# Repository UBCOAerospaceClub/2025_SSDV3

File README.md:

# The Super Step Down V3

The SSDV3 is an independently-made, non-isolated DC/DC converter designed for unmanned aerial systems (UAS). The module is intended for converting 50V battery input down to 5-12V output at a maximum load of 8A. It acts as a reliable battery-eliminator circuit (BEC) through effective regulation in the presence of large line voltage and load current transients.

## Comparison with Last Super Step Down

This design is motivated by the challenges encountered by the [UBCO Aerospace Club](https://github.com/UBCOAerospaceClub) with their Jellyfish quadcopter when powering auxiliary electronics off the drone's main battery. Lessons were learned through a variety of integration failures, investigations, and verification, and these experiences informed the development of version 3 of the Super Step Down series.

**Improvements from the previous version:**

- Dramatically improved regulation during line and load transients
- Considerable footprint area reduction by 16.5%
- Configurable output voltages instead of a fixed 5V output
- Added ESD protection on inputs
- Features reverse polarity protection
- Uses direct solder pads instead of terminal block for output connection

## Documentation

[Super Step Down V3 Documentation](https://docs.google.com/document/d/1HDTwUbcQu91JqGZ-epUO-CT9nVxvoZJ6mtjSmItczHE/edit?usp=sharing)

## Specifications

<table><tbody>
  <tr>
    <td>Input Voltage</td>
    <td>20-60V</td>
  </tr>
  <tr>
    <td>Max Transient Voltage</td>
    <td>100V (clamping starts at 70V)</td>
  </tr>
  <tr>
    <td>Output Voltage(s)</td>
    <td>5.1V, 7.4V, 12V</td>
  </tr>
  <tr>
    <td>Max Output Current*</td>
    <td>8A</td>
  </tr>
  <tr>
    <td>Typical Efficiency</td>
    <td>88%</td>
  </tr>
  <tr>
    <td>Voltage Transient Deviation</td>
    <td>±2.5%</td>
  </tr>
</tbody>
</table>

### Performance Curves

**Voltage ripple at 5.1V Output**

**Transient response of 5.1V 5-0A Output**

**Efficiency Measurements, 50-V Input**

## Copyright Notice

Copyright &#169; Julian Joaquin 2026

Documentation and media are licensed under CC BY-SA 4.0

Hardware Source Licensed under CERN-OHL-W version 2

UBCO is registered trademark of the University of British Columbia. The use of UBC trademarks in this project are only for identification, and do not indicate association or endorsement. For guidelines on the permitted uses of UBC trademarks, please see http://universitycounsel.ubc.ca/university-trade-marks/.

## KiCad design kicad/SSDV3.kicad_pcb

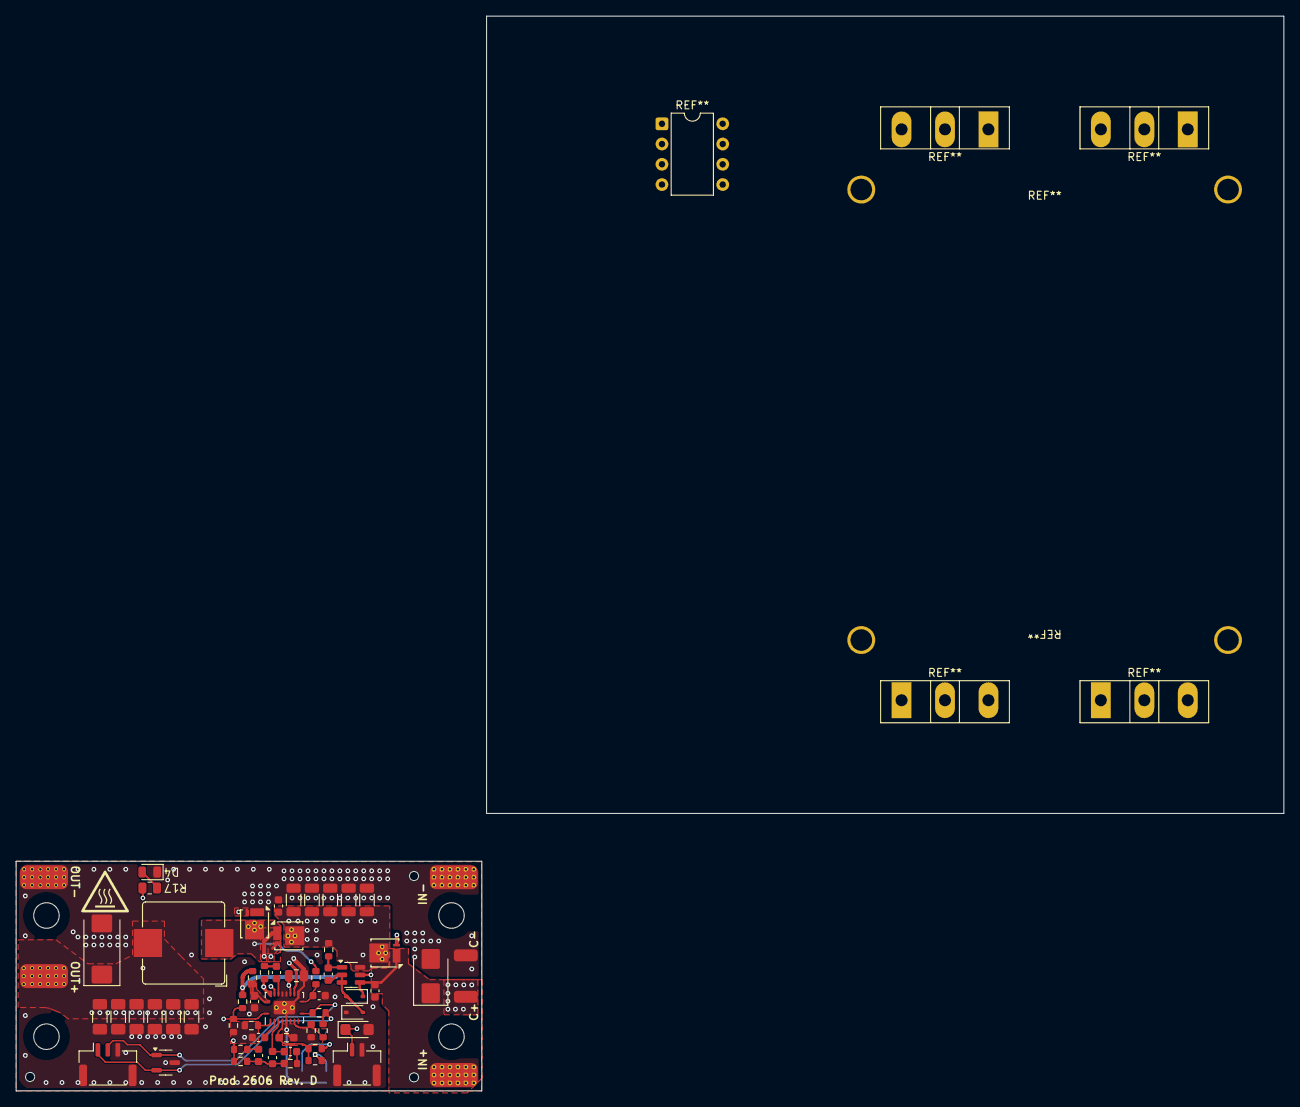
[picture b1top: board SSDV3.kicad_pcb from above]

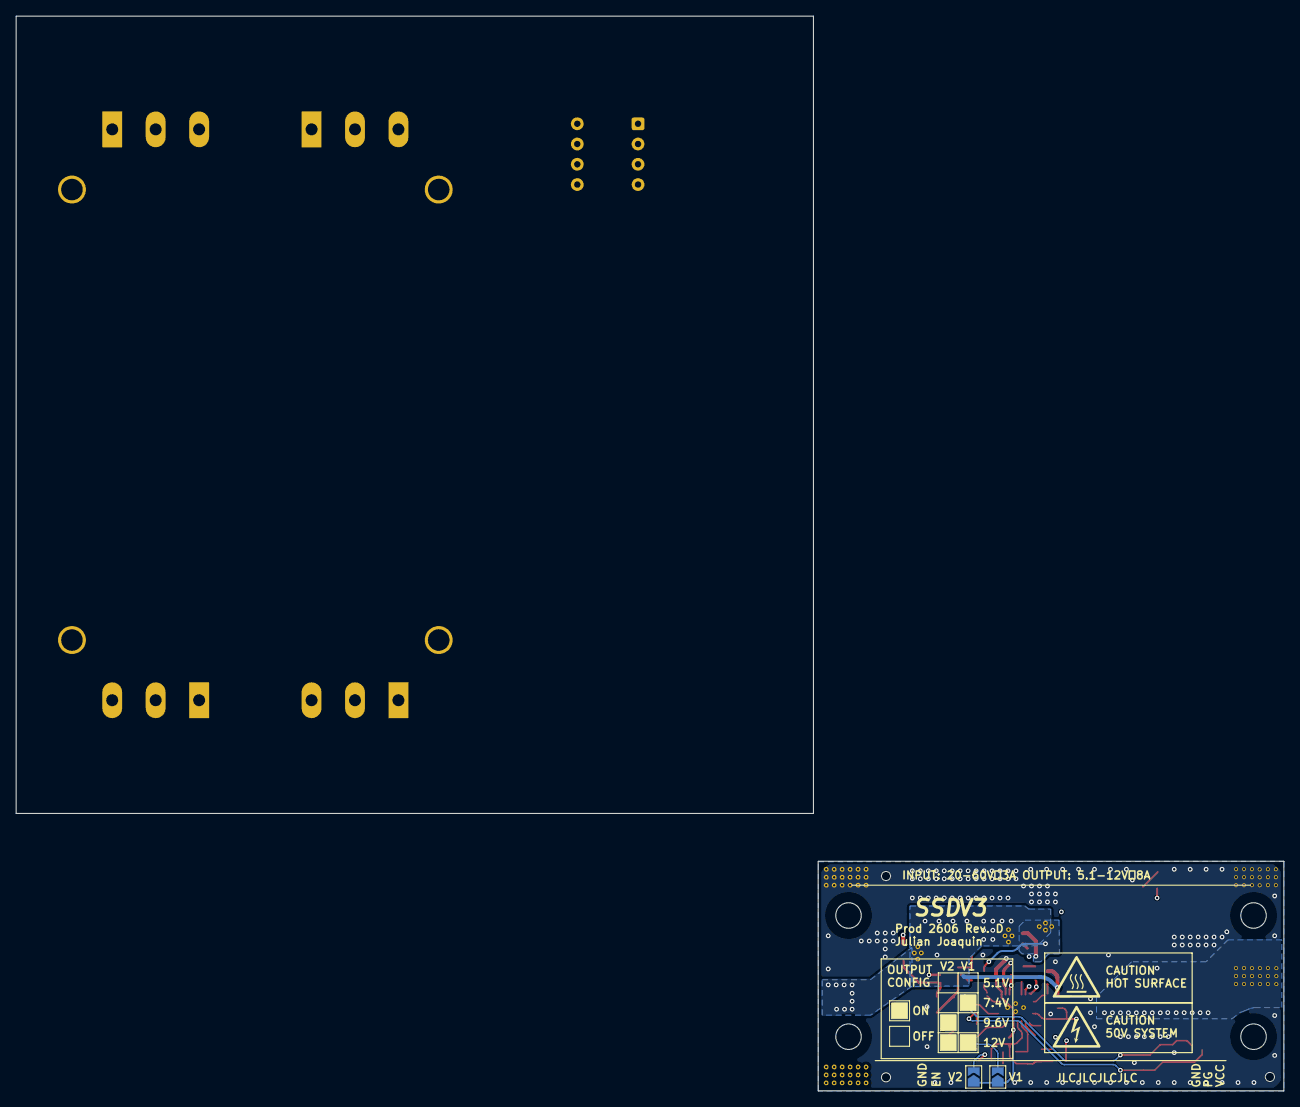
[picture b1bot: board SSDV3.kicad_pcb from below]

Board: 4 copper layers, 58.4 x 28.8 mm, 67 parts (3 on the bottom side), 28 nets.

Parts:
C2, C3, C4, C10, C13: 100nF; C_0603_1608Metric
C5, C6, C7, C8, C9: 4.7uF; C_1206_3216Metric
C11: 2.2uF; C_0805_2012Metric
C12: 47nF; C_0603_1608Metric
C14: 8.2pF; C_0603_1608Metric
C15: 1.5nF; C_0603_1608Metric
C16: 4.7nF; C_0603_1608Metric
C17: 68pF; C_0603_1608Metric
C18, C19, C20, C21, C22, C23: 22uF; C_1206_3216Metric_Pad1.33x1.80mm_HandSolder
C24: 100uF; CP_EIA-7343-20_Kemet-V_HandSolder
D1: 64V; D_SMB
D2, D3: BAT46WS; D_SOD-323
D4: GREEN; LED_0805_2012Metric
D5: 60V; D_SMF
D6: 8V; SOT-23-3
H1, H2, H3: MountingHole; ToolingHole_1.152mm
HS1: 241802B92200G; 24180xB9x200G
J1, J4, J5, J6: SolderPad; SolderWirePad_1x01_SMD_3x6mm
J2, J3: SolderPad; SolderWirePad_1x01_SMD_1.5x3mm
J7: SM02B-GHS-TB(LF)(SN); JST_GH_SM02B-GHS-TB_1x02-1MP_P1.25mm_Horizontal
J8: SM03B-GHS-TB(LF)(SN); JST_GH_SM03B-GHS-TB_1x03-1MP_P1.25mm_Horizontal
JP1: 7.4V; SolderJumper-2_P1.3mm_Open_TrianglePad1.0x1.5mm
JP2: 9.6V; SolderJumper-2_P1.3mm_Open_TrianglePad1.0x1.5mm
L1: 4.7uH; L_Bourns_SRP1038C_10.0x10.0mm
NT1: NetTie_2; NetTie-2_SMD_Pad0.5mm
Q1, Q2, Q3: BSZ146N10LS5; Infineon_PG-TSDSON-8-26_3.3x3.3mm_P0.65mm_ThermalVias-D0.3mm
R1, R11: 1.5k; R_0603_1608Metric
R2: 150k; R_0603_1608Metric
R3: 12k; R_0603_1608Metric
R4, R9: 2.2; R_0603_1608Metric
R5: 24k; R_0603_1608Metric
R6, R8, R12: 20k; R_0603_1608Metric
R7: 0; R_0603_1608Metric
R10: 560; R_0603_1608Metric
R13: 10k; R_0603_1608Metric
R14: 6.81k; R_0603_1608Metric
R15: 3.48k; R_0603_1608Metric
R16: 3.74k; R_0603_1608Metric_Pad0.98x0.95mm_HandSolder
R17: 1k; R_0805_2012Metric
U1: LM5050-1; TSOT-23-6
U2: LM5146; Texas_RGY0020B_EP_3.5x4.5mm_P0.5mm_ThermalVias-D0.3mm

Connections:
/buck_converter/BST: C13.2, U2.17 (BST)
/buck_converter/COMP: C16.1, C17.2, U2.4 (COMP)
/buck_converter/COMP_RC1: C16.2, R13.2
/buck_converter/COMP_RC2: C15.1, R11.2
/buck_converter/FB: C15.2, C17.1, R12.2, R13.1, R14.1, R15.1, R16.1, U2.5 (FB)
/buck_converter/HO: Q2.2 (G), U2.18 (HO)
/buck_converter/ILIM: C14.1, R10.2, U2.11 (ILIM)
/buck_converter/JP_CFG1: JP1.2 (B), R14.2
/buck_converter/JP_CFG2: JP2.2 (B), R15.2
/buck_converter/LO: Q3.2 (G), U2.13 (LO)
/buck_converter/RBST: C13.1, R9.1
/buck_converter/RT: R5.1, U2.2 (RT)
/buck_converter/SS_TRK: C12.1, U2.3 (SS_TRK)
/buck_converter/SW: L1.1, Q2.1 (S), Q3.3 (D), R9.2, R10.1, U2.19 (SW)
/buck_converter/SYNCIN: R6.2, R7.1, U2.8 (SYNCIN)
/buck_converter/U2_VIN: C4.1, R4.2, U2.20 (VIN)
/buck_converter/VOUT_LED: D4.2 (A), R17.2
/rpp/U1_GATE: Q1.2 (G), U1.5 (GATE)
/rpp/U1_GND: C3.2, D2.2 (A), D3.2 (A), U1.2 (GND), U1.3 (OFF)
/rpp/U1_VS: C3.1, R1.2, U1.1 (VS)
AGND: C12.2, JP1.1 (A), JP2.1 (A), NT1.2, R3.2, R5.2, R7.2, R16.2, U2.6 (AGND)
PG: D6.1 (K), J8.2, R8.2, U2.10 (PGOOD)
PGND: C2.2, C4.2, C5.2, C6.2, C7.2, C8.2, C9.2, C10.2, C11.2, C14.2, C18.2, C19.2, C20.2, C21.2, C22.2, C23.2, C24.2, D1.2 (A2), D3.1 (K), D4.1 (K), D5.2 (A2), D6.3 (A), J3.1, J4.1, J6.1, J7.2, J7.MP (MountPin), J8.3, J8.MP (MountPin), NT1.1, Q3.1 (S), U2.12 (PGND), U2.15 (EP), U2.16 (NC), U2.21 (EP)
U2_EN: D5.1 (A1), J7.1, R2.2, R3.1, U2.1 (EN_UVLO)
VBAT: C2.1, D1.1 (A1), D2.1 (K), J1.1, Q1.1 (S), U1.4 (IN)
VCC: C11.1, D6.2 (K), J8.1, R6.1, R8.1, U2.14 (VCC)
VIN: C5.1, C6.1, C7.1, C8.1, C9.1, C10.1, J2.1, Q1.3 (D), Q2.3 (D), R1.1, R2.1, R4.1, U1.6 (OUT)
VOUT: C18.1, C19.1, C20.1, C21.1, C22.1, C23.1, C24.1, J5.1, L1.2, R11.1, R12.1, R17.1

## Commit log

2025-11-09 Adjusted licensing for club
2025-11-09 Revise copyright notice and add trademark information
    Updated copyright section and added trademark notice.
2025-11-23 Added heatsink footprint
2025-12-02 Addressed HS FET failure mode from revC
2025-12-17 Created redesign for revD to reduce thermal stress
2026-01-30 Added test waveforms and library changes
2026-02-02 FET Optimizations
2026-02-06 RevD finished
2026-02-06 Fix image paths in README.md for performance curves
2026-02-06 Wrong design files initially commited
2026-02-07 Added UBCO trademark notice, prepared for production
2026-02-07 Final production files
2026-02-07 Component optimizations
2026-02-08 Minor technical corrections
2026-05-12 Rev D production photos and 3D render
2026-05-12 Start of Rev E
2026-05-14 Added documentation
2026-05-17 RevE New symbols and footprints
2026-05-20 Revised docs
